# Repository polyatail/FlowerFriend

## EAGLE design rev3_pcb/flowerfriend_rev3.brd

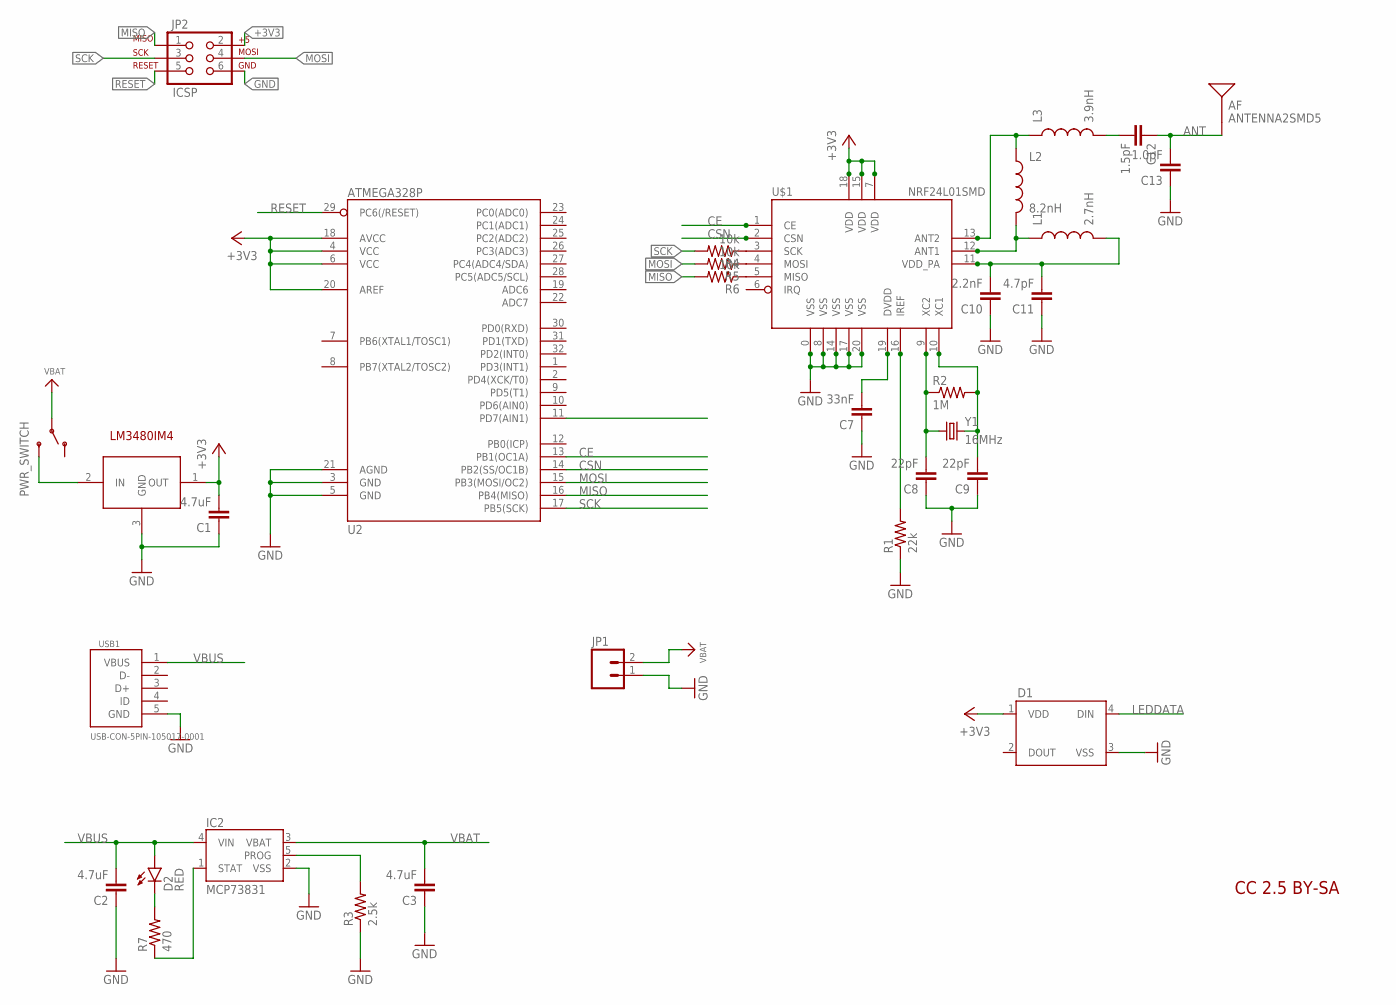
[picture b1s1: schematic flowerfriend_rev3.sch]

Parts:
AF: ANTENNA2SMD5; ANTENNA-CHIP5
C1, C2, C3: 4.7uF; 0805
C7: 33nF; 0805
C8, C9: 22pF; 0805
C10: 2.2nF; 0805
C11: 4.7pF; 0805
C12: 1.5pF; 0805
C13: 1.0pF; 0805
D1: WS2812B
D2: RED; LED-0603
IC1: LM3480IM4; SOT23-3
IC2: MCP73831; SOT23-5
JP1: M02PTH; 1X02
JP2: ICSP; 2X3
L1: 2.7nH; 0805
L2: 8.2nH; 0805
L3: 3.9nH; 0805
PWR_SWITCH: SWITCH_SPDT; KPS-1290
R1: 22k; 0805
R2: 1M; 0805
R3: 2.5k; 0805
R4, R5, R6: 10k; 0805
R7: 470; 0805
U2: ATMEGA328P; TQFP32-08
U$1: NRF24L01SMD; QFN20
USB1: USB-CON-5PIN-105017-0001; USB-MICRO-MOLEX-105017-0001
Y1: 16MHz; CRYSTAL-SMD-5X3

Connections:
+3V3: C1.2, D1.1 (VDD), IC1.1 (OUT), JP2.2, U2.4 (VCC), U2.6 (VCC), U2.18 (AVCC), U2.20 (AREF), U$1.7 (VDD), U$1.15 (VDD), U$1.18 (VDD)
ANT: AF.FEED, C12.1, C13.2
CE: U2.13 (PB1(OC1A)), U$1.1 (CE)
CSN: U2.14 (PB2(SS/OC1B)), U$1.2 (CSN)
GND: C1.1, C2.1, C3.1, C7.1, C8.1, C9.1, C10.1, C11.1, C13.1, D1.3 (VSS), IC1.3 (GND), IC2.2 (VSS), JP1.1, JP2.6, R1.1, R3.1, U2.3 (GND), U2.5 (GND), U2.21 (AGND), U$1.0 (VSS), U$1.8 (VSS), U$1.14 (VSS), U$1.17 (VSS), U$1.20 (VSS), USB1.5 (GND)
LEDDATA: D1.4 (DIN), U2.11 (PD7(AIN1))
MISO: JP2.1, R6.2, U2.16 (PB4(MISO))
MOSI: JP2.4, R5.2, U2.15 (PB3(MOSI/OC2))
unnamed: IC2.5 (PROG), R3.2
unnamed: C8.2, R2.1, U$1.9 (XC2), Y1.1
unnamed: C9.2, R2.2, U$1.10 (XC1), Y1.3 (2)
unnamed: R4.1, U$1.3 (SCK)
unnamed: R5.1, U$1.4 (MOSI)
unnamed: L2.1, L3.1, U$1.13 (ANT2)
unnamed: C10.2, C11.2, L1.2, U$1.11 (VDD_PA)
unnamed: R1.2, U$1.16 (IREF)
unnamed: C7.2, U$1.19 (DVDD)
unnamed: L1.1, L2.2, U$1.12 (ANT1)
unnamed: C12.2, L3.2
unnamed: R6.1, U$1.5 (MISO)
unnamed: IC1.2 (IN), PWR_SWITCH.S
unnamed: D2.C, R7.2
unnamed: IC2.1 (STAT), R7.1
RESET: JP2.5, U2.29 (PC6(/RESET))
SCK: JP2.3, R4.2, U2.17 (PB5(SCK))
VBAT: C3.2, IC2.3 (VBAT), JP1.2, PWR_SWITCH.P
VBUS: C2.2, D2.A, IC2.4 (VIN), USB1.1 (VBUS)

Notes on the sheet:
CC 2.5 BY-SA

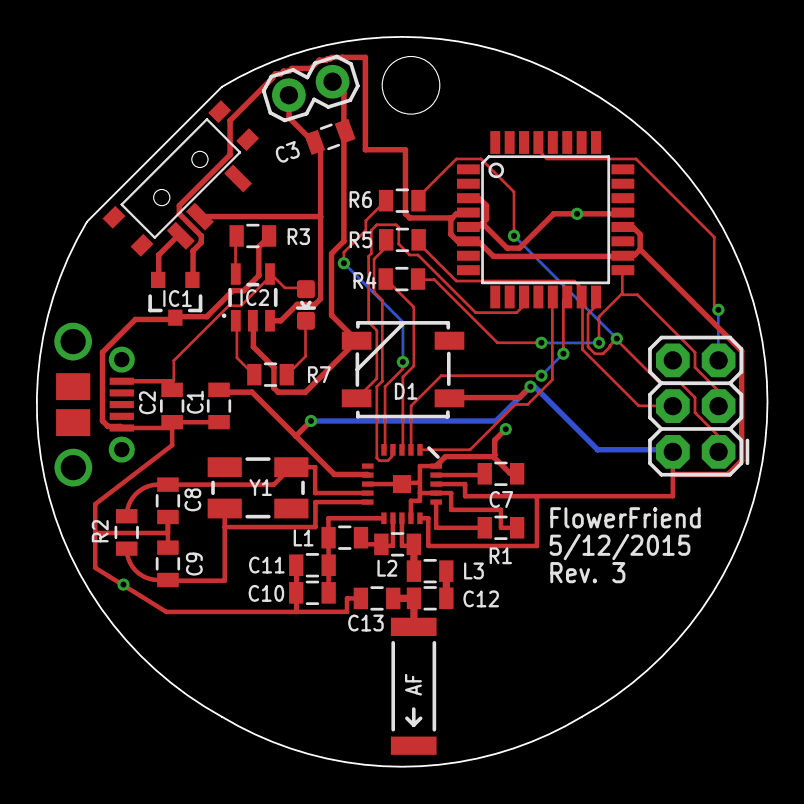
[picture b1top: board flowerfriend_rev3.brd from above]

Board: 2 copper layers, 40.6 x 40.5 mm, 33 parts (1 on the bottom side), 27 nets.

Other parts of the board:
U$2: ADAFRUIT_30MM

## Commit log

2015-05-11 Few small changes to get sync working
2015-05-11 Rename to RF_ADDR
2015-05-11 Change debugging messages to save SRAM while running
2015-05-11 Colors fade rather than change abruptly
2015-05-11 Cleanup debug messages, add flashing upon syncing
2015-05-11 Code cleanup
2015-05-12 Add a few features to smooth out the display
2015-05-19 Small comment changes
2015-05-19 Reduce memory footprint and packet size
2015-05-19 Using newly freed packet space, share up to 13 mesh TTLs per packet
2015-05-19 Flash unique color upon startup
2015-05-19 Lower fuzz seems to give the appearance of faster syncing
2015-07-10 Small changes to potentially help with range - Resend packets multiple times at every send - Use Channel 10 which is closer to center frequency and below WiFi - Use PA_MAX because PA_HIGH isn't reall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
2015-07-12 Make flowers sync more nicely
2015-07-15 Introduce new packet type for syncing
2015-07-15 Reorganize RF code into functions
2015-07-23 Play with TTLs to get better performance
2015-07-24 Completely revamp mesh packet style
2015-07-24 Checking in accessory code
2015-08-10 Drastically reduced packet size and small tweaks
2015-08-10 Changes that might fix syncing problem There is a scenario where a unit will receive a packet, sync to it by switching colors, and then in the same iteration, it will switch to the next-next color. T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
2015-09-11 Sync tweaks
2015-09-11 Checking in PCB designs
2015-09-11 Organizing

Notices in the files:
parts and their libraries:
microbuilder: This work is placed in the public domain, and may be freely used for commercial and non-commercial work with the following conditions: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
SparkFun: Licensing: CC v3.0 Share-Alike You are welcome to use this library for commercial purposes.
